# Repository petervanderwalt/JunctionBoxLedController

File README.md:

# JunctionBoxLedController
JunctionBoxLedController

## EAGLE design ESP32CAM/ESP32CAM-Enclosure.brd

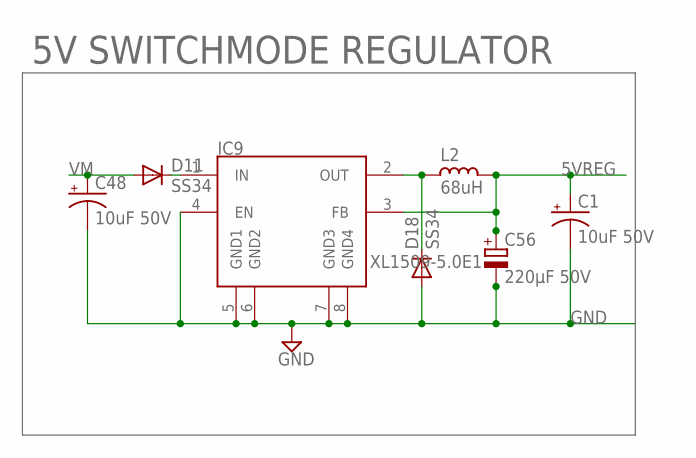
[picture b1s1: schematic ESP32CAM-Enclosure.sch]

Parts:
C1, C48: 10uF 50V; EIA3216
C56: 220µF 50V; E3,5-10
D11, D18: SS34; DO-214AC
IC9: XL1509-5.0E1; SO08
L2: 68uH; CD75

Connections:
5VREG: C1.A (+), C56.+, IC9.3 (FB), L2.1
GND: C1.C (-), C48.C (-), C56.-, D18.2 (A), IC9.4 (EN), IC9.5 (GND1), IC9.6 (GND2), IC9.7 (GND3), IC9.8 (GND4)
unnamed: D18.1 (C), IC9.2 (OUT), L2.2
unnamed: D11.1 (C), IC9.1 (IN)
VM: C48.A (+), D11.2 (A)

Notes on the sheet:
5V SWITCHMODE REGULATOR

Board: 2 copper layers, 7 parts (0 on the bottom side), 5 nets, no tracks yet.

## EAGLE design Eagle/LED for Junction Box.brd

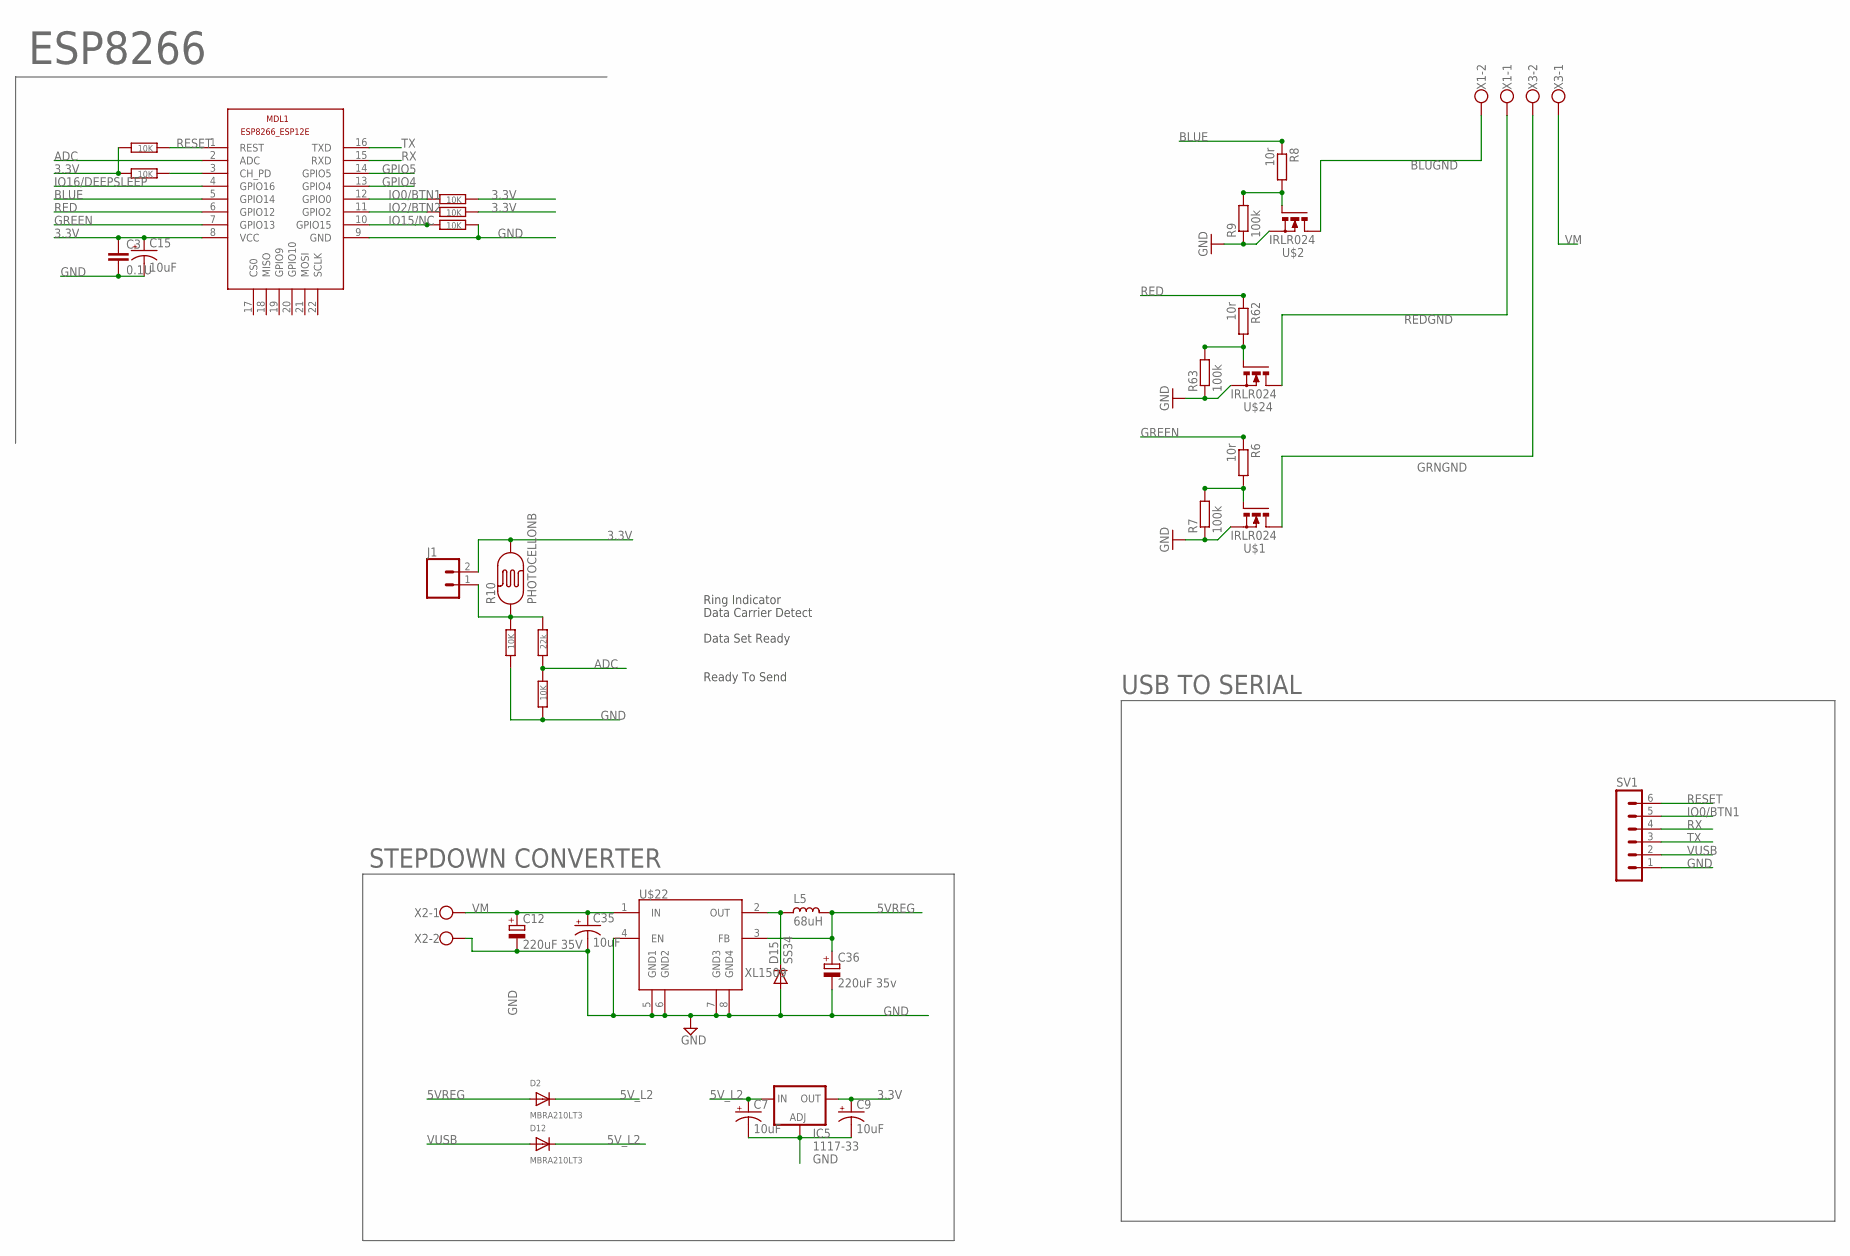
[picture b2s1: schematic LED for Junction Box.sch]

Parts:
C3: 0.1U; C1206
C7, C9, C15, C35: 10uF; EIA3216
C12: 220uF 35V; E3,5-8
C36: 220uF 35v; E3,5-8
D2, D12: MBRA210LT3; SMADIODE
D15: SS34; DO-214AC
IC5: 1117-33; SOT223
J1: CONN_02LOCK; 1X02_LOCK
L5: 68uH; CD75
MDL1: ESP8266-12EESP8266-ESP12E; ESP8266-ESP12E
R3: 22k; R1206
R4, R5, R11, R12, R28, R29, R31: 10K; R1206
R6, R8, R62: 10r; R1206
R7, R9, R63: 100k; R1206
R10: PHOTOCELLONB; ON_BOARD
SV1: MA06-1
U$1, U$2, U$24: IRLR024; D-PAK_TO252AA
U$22: XL1509; SO08
X1, X2, X3: W237-102

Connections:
3.3V: C3.1, C9.A (+), C15.A (+), IC5.4 (OUT), J1.2, MDL1.8 (VCC), R10.2, R11.2, R12.2, R28.1, R29.1
5VREG: C36.+, D2.A, L5.1, U$22.3 (FB)
5V_L2: C7.A (+), D2.C, D12.C, IC5.3 (IN)
ADC: MDL1.2 (ADC), R3.1, R4.2
BLUE: MDL1.5 (GPIO14), R8.1
BLUGND: U$2.4 (D), X1.2
GND: C3.2, C7.C (-), C9.C (-), C12.-, C15.C (-), C35.C (-), C36.-, D15.2 (A), IC5.1 (ADJ), MDL1.9 (GND), R4.1, R5.1, R7.1, R9.1, R31.2, R63.1, SV1.1, U$1.3 (S), U$2.3 (S), U$22.4 (EN), U$22.5 (GND1), U$22.6 (GND2), U$22.7 (GND3), U$22.8 (GND4), U$24.3 (S), X2.2
GPIO4: MDL1.13 (GPIO4)
GPIO5: MDL1.14 (GPIO5)
GREEN: MDL1.7 (GPIO13), R6.1
GRNGND: U$1.4 (D), X3.2
IO0/BTN1: MDL1.12 (GPIO0), R12.1, SV1.5
IO2/BTN2: MDL1.11 (GPIO2), R11.1
IO15/NC: MDL1.10 (GPIO15), R31.1
IO16/DEEPSLEEP: MDL1.4 (GPIO16)
unnamed: R62.2, R63.2, U$24.1 (G)
unnamed: D15.1 (C), L5.2, U$22.2 (OUT)
unnamed: R6.2, R7.2, U$1.1 (G)
unnamed: R8.2, R9.2, U$2.1 (G)
unnamed: J1.1, R3.2, R5.2, R10.1
unnamed: MDL1.3 (CH_PD), R28.2
RED: MDL1.6 (GPIO12), R62.1
REDGND: U$24.4 (D), X1.1
RESET: MDL1.1 (REST), R29.2, SV1.6
RX: MDL1.15 (RXD), SV1.4
TX: MDL1.16 (TXD), SV1.3
VM: C12.+, C35.A (+), U$22.1 (IN), X2.1, X3.1
VUSB: D12.A, SV1.2

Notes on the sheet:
ESP8266
Ring Indicator
Data Carrier Detect
Data Set Ready
Ready To Send
STEPDOWN CONVERTER
USB TO SERIAL

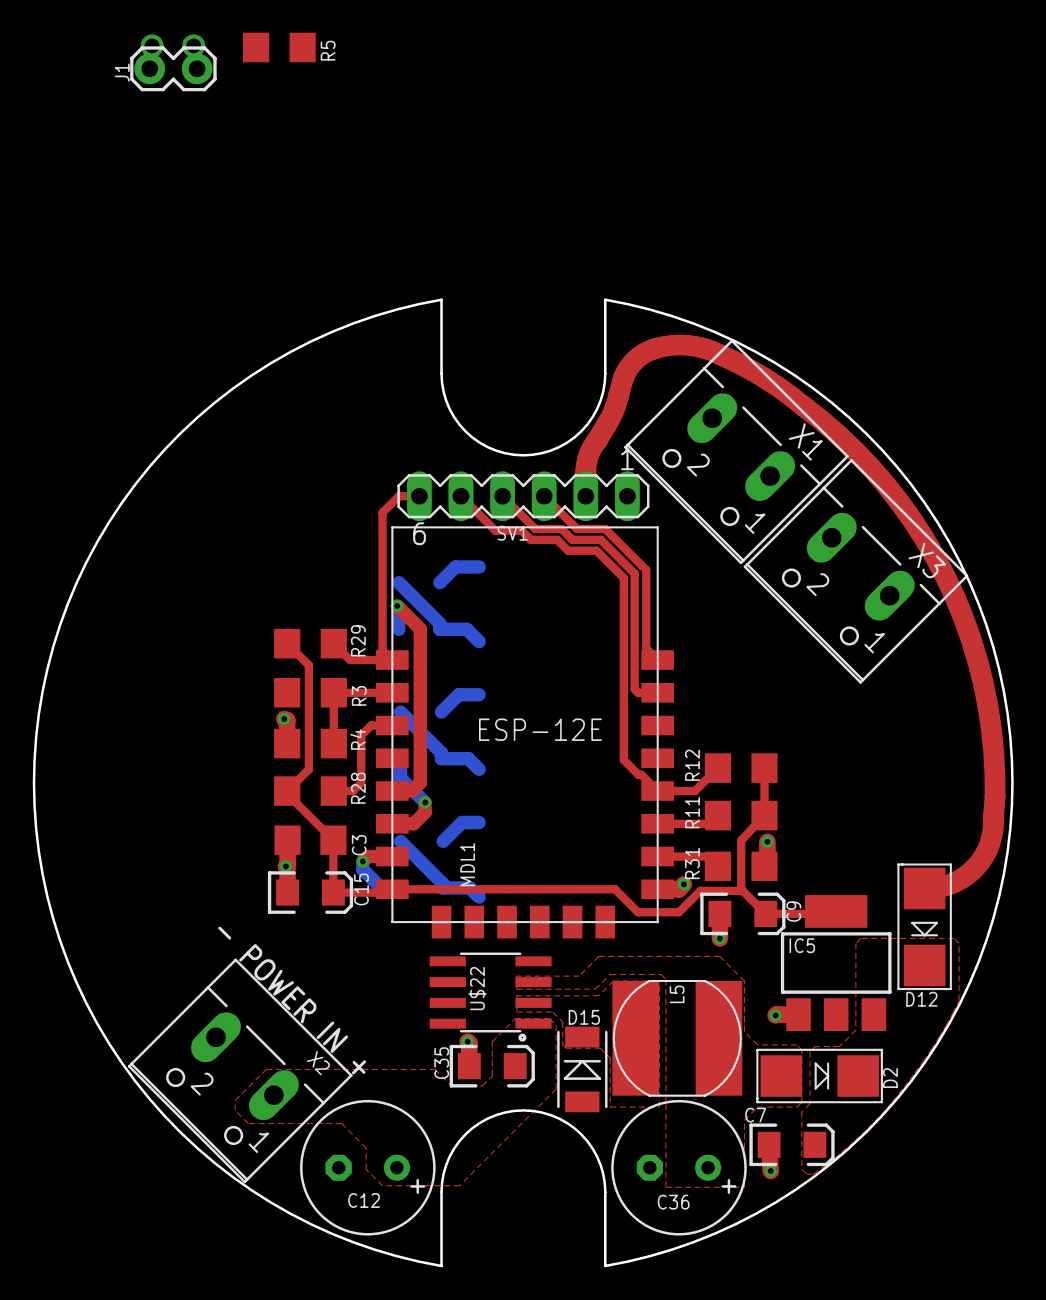
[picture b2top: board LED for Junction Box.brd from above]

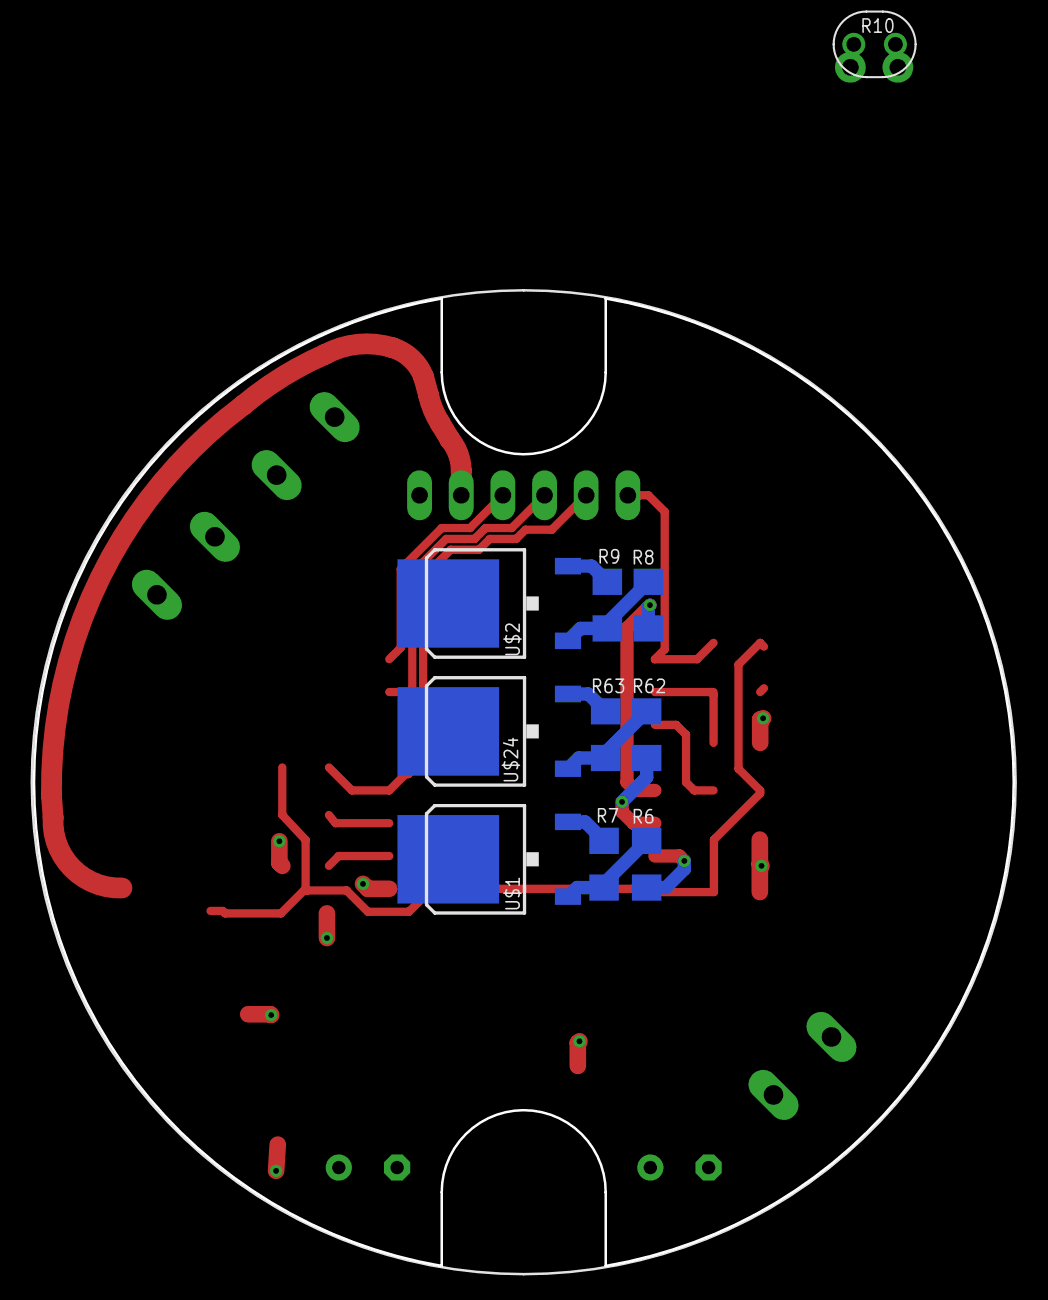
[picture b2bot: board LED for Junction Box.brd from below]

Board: 2 copper layers, 59.7 x 59.0 mm, 37 parts (10 on the bottom side), 25 nets.

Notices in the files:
parts and their libraries:
rc-master-smd: Copyright (C) 2007, Bob Starr
SparkFun-Connectors: Licensing: Creative Commons ShareAlike 4.0 International - https://creativecommons.org/licenses/by-sa/4.0
